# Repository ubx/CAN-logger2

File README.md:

# ESP32 CAN Logger for CANaerospace with WiFi File Browser

This project implements a **dual-mode ESP32 application** for capturing and storing CAN bus data onto an SD card, \
while also providing a temporary WiFi access point with a web-based file browser to retrieve logged data.

---

## Features

### WiFi File Browser
- **WiFi SoftAP Setup** with WPA/WPA2 authentication.
- **Dynamic SSID Generation** based on ESP32 MAC address.
- **Web-based File Browser**:
  - Displays SD card files in a clean HTML table.
  - Supports file size display in human-readable format (KB, MB, GB).
  - Click-to-download functionality with MIME type detection.
- **Automatic Session Timeout**
  - Tracks last HTTP activity.
  - Shuts down after configurable inactivity time.
---

### CAN Logging System
- **CAN Bus Support (TWAI Driver)**
  - Configured for **500 kbit/s**.
  - Accepts all CAN frames.
  - Reliable driver startup with retry on failure.
- **SD Card Logging**
  - Files named sequentially as `CANxxxxx.LOG`.
  - Automatic **old file cleanup** if free space < 2 GB (reclaims up to 4 GB).
  - Efficient batch writes with **32 KB buffering**.
  - Uses `fsync()` to ensure data integrity.
- **Logging Format**
  - Each CAN frame stored as:
    ```
    (timestamp) can <ID>#<DATA>
    ```  
    Example:
    ```
    (1755839938.123456) can 123#11AAFF
    ```
- **Task-based Architecture**
  - `CAN_RX Task`: Receives frames from TWAI driver.
  - `CAN_Proc Task`: Formats messages into log lines.
  - `SD_Writer Task`: Buffers and writes batches to SD card.
- **Runtime Monitoring**
  - Tracks total message count.
  - Periodic logging of statistics to console.

---

## Technical Highlights
- **FreeRTOS Queues** for decoupled CAN reception and SD writing.
- **High-throughput SD logging** using buffered I/O.
- **Failsafe Storage Management** with automatic cleanup.
- **Lightweight Web Server** (ESP-IDF HTTPD) for SD browsing and downloads.
- **No RTC dependency**: Uses a fictional start timestamp to emulate Unix time.
- **Tested on an ESP32-S3 board:** [ESP32-S3 1.64inch AMOLED Touch Display Development Board](https://www.waveshare.com/esp32-s3-touch-amoled-1.64.htm) with a SANDISK Ultra \
  64 GB, microSDXC, U1, UHS-I.
- **Performance Test**: Running `cangen can0 -D i -I i -L 4 -g 0.5` resulted in a transmission rate of \
approximately 1,800 messages per second.
- **Power consumption**: Web server: 473 mW; Logger with display on: 420 mW; Logger with display off: 440 mW.
---

## Typical Use Case
1. **Power up device** → ESP32 starts in **WiFi AP mode** with SD card accessible via browser.
2. **Download / inspect past CAN logs** through the web interface.
3. **After inactivity timeout** → Device switches into **logging mode**, continuously recording
4. CAN traffic onto the SD card.

---

## Pin-to-Pin Wiring Table

| ESP32 Pin | Function       | Connected To                | Notes                        |
|-----------|----------------|-----------------------------|------------------------------|
| GPIO1     | SPI MOSI       | SD Card MOSI                | Data out from ESP32 → SD     |
| GPIO3     | SPI MISO       | SD Card MISO                | Data in from SD → ESP32      |
| GPIO2     | SPI SCLK       | SD Card SCLK                | SPI clock                    |
| GPIO41    | SPI CS         | SD Card CS                  | Chip select                  |
| GPIO9     | CS             | LCD Chip Select             | Active low                   |
| GPIO10    | PCLK           | LCD SPI Clock / Pixel Clock | QSPI clock                   |
| GPIO11    | DATA0          | LCD Data 0 (D0)             | QSPI data line               |
| GPIO12    | DATA1          | LCD Data 1 (D1)             | QSPI data line               |
| GPIO13    | DATA2          | LCD Data 2 (D2)             | QSPI data line               |
| GPIO14    | DATA3          | LCD Data 3 (D3)             | QSPI data line               |
| GPIO21    | RST            | LCD Reset                   | Optional, active low         
| GPIO18    | CAN TX         | CAN Transceiver TXD         | Transmit to CAN bus          |
| GPIO17    | CAN RX         | CAN Transceiver RXD         | Receive from CAN bus         |
| 3V3       | Power          | SD Card VCC, CAN VCC        | Ensure 3.3V compatible       |
| GND       | Ground         | SD Card GND, CAN GND        | Common ground reference      |
| CANH/—    | —              | CAN Bus High Line           | Differential bus line        |
| CANL/—    | —              | CAN Bus Low Line            | Differential bus line        |

## Recommended Parts List

### Core Components
- **ESP32 Development Board**
  - Example: ESP32-DevKitC, ESP32-WROOM, or M5Stack Core (if display/UI desired)
  - Must expose SPI pins and GPIOs used in the project

- **SD Card Module (SPI interface)**
  - Example: MicroSD Card Module (3.3V logic, SPI mode support)
  - Ensure 3.3V compatible (no 5V modules without level shifting)
  - MicroSD card, Class 10, A1 or higher, ≥16 GB recommended

- **CAN Transceiver** (connects ESP32 to CAN bus)
  - Example ICs:
    - SN65HVD230 (3.3V, commonly used with ESP32)
    - MCP2551 (5V, requires level shifting for ESP32)
    - TJA1050 (5V, also requires level shifting)
  - Choose based on bus voltage (3.3V-friendly parts are easier)

### Power & Connectivity
- **Stable 5V Supply** (for ESP32 board)
  - ESP32 boards usually regulate down to 3.3V internally
- **Common Ground Reference** between ESP32, SD card, and CAN transceiver
- **CAN Bus Wiring**
  - Twisted pair cable (for CANH & CANL)
  - 120 Ω termination resistors at both bus ends

### Optional / Helpful
- **MicroSD Card Reader** (for PC, to inspect logs directly if needed)
- **USB-to-CAN Adapter** (for testing/logging against a PC CAN interface)
- **Case/Enclosure** to protect the ESP32 + modules in automotive environment
- **For CANaerospace logs**: use [this program](https://github.com/ubx/canlog-correct-ts/blob/master/correct-ts.py) to adjust timestamps.
- **Format SD card**: use [this tool](https://www.sdcard.org/downloads/sd-memory-card-formatter-for-linux/)

### Bill of materials

| Number | Part                                                          | Qty | Picture                                          | 	Source                                                                                                                                                        |
|--------|---------------------------------------------------------------|-----|--------------------------------------------------|----------------------------------------------------------------------------------------------------------------------------------------------------------------|
| 1      | ESP32-S3 1.64inch AMOLED<br/> Touch Display Development Board | 1   |   | [AMOLED Touch Display<br/>Development Board](https://www.waveshare.com/esp32-s3-touch-amoled-1.64.htm)                                                         |                                                                                
| 2      | SN65HVD230 CAN Board                                          | 1   |         | [SN65HVD230 CAN Board	](https://www.waveshare.com/sn65hvd230-can-board.htm)                                                                                    |                                                                                      |
| 3      | Step Down Converter Modul                                     | 1   |         | [Step Down Converter Modul	](https://de.aliexpress.com/item/1005006461126809.html?spm=a2g0o.order_list.order_list_main.76.1a475c5fBDXy9Z&gatewayAdapt=glo2deu) |
| 4      | M12 5 Pin Cable Connector                                     | 1   |  | [M12 5 Pin Cable Connector](https://de.aliexpress.com/item/1005008983446794.html?spm=a2g0o.order_list.order_list_main.60.1a475c5fBDXy9Z&gatewayAdapt=glo2deu)  |
| 5      | micro sd card                                                 | 1   |                      |
| 6      | M2x5 round screw                                              | 4   |                                                  |                                                                                                                                                                |
| 7      | M2.5x5 countersunk screw                                      | 1   |
| 8      | M2.5x4 insert                                                 | 1   |
| 9      | Optional:<br/>SD-TF-extension-cable                           | 1   |        | [SD-TF-extension-cable	](https://de.aliexpress.com/item/1005005671622003.html?spm=a2g0o.order_list.order_list_main.4.3fb05c5fkolpFm&gatewayAdapt=glo2deu)      |

---

## Troubleshooting: sdQueue full / canQueue full warnings
If you see warnings like:
- W (xxxx) CAN_Proc: sdQueue full, dropped line
- W (xxxx) CAN_RX: canQueue full, dropped

it means the producer tasks (CAN reception/formatting) are temporarily faster than the consumer (SD writer). \
The firmware includes several mitigations:

Additional steps you can take
- Use a fast SD card (A1/A2 or High Endurance) and keep it healthy/formatted (FAT32).
- Reduce other workload while logging (disable unnecessary peripherals, WiFi, or display if not needed).
- If you still experience drops, you can increase queue depths in src/logger/logging.cpp:
  - CAN_QUEUE_LEN: number of CAN frame buffered between driver and formatter.
  - SD_QUEUE_LEN: number of formatted lines buffered before SD writing.
    Be mindful that increasing these consumes internal RAM.
- If your board has PSRAM, keep it enabled. The logger uses a large batch buffer to write in big chunks for higher throughput.
- Ensure stable 3.3 V supply. Brownouts can slow peripherals and the filesystem.

Notes
- Even with a high-rate CAN traffic (e.g., ~1200 msgs/s), a proper SD card and power supply should avoid drops in most cases.
- If absolute losslessness is required, consider reducing CAN bus load, increasing queue sizes, or writing in binary \
to reduce per-message overhead.

## Todo
- Check display z-distance.
- PCB, move modules up 2mm z-distance.
- PCB, bigger holes for CAN connector cables.
- Check usb hole, make it more tolerant.
- Better lid locking.

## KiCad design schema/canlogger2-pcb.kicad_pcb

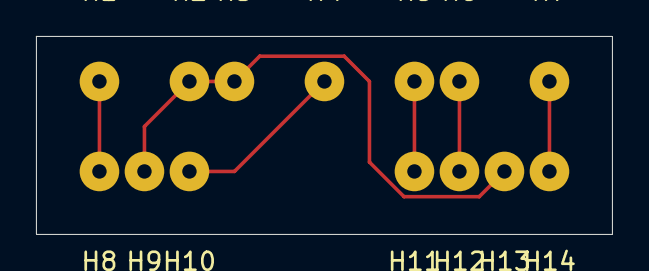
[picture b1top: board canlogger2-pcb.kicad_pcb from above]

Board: 2 copper layers, 32.0 x 11.0 mm, 14 parts (0 on the bottom side), 6 nets.

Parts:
H1: 5V; ConnectingHole_0.8mm_M2_DIN965_Pad
H2, H3, H9, H13: GND; ConnectingHole_0.8mm_M2_DIN965_Pad
H4: 12V; ConnectingHole_0.8mm_M2_DIN965_Pad
H5: Tx; ConnectingHole_0.8mm_M2_DIN965_Pad
H6: Rx; ConnectingHole_0.8mm_M2_DIN965_Pad
H7, H14: 3.3V; ConnectingHole_0.8mm_M2_DIN965_Pad
H8: Vo; ConnectingHole_0.8mm_M2_DIN965_Pad
H10: Vi; ConnectingHole_0.8mm_M2_DIN965_Pad
H11: TX; ConnectingHole_0.8mm_M2_DIN965_Pad
H12: RX; ConnectingHole_0.8mm_M2_DIN965_Pad

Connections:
unnamed: H1.1, H8.1
unnamed: H4.1, H10.1
unnamed: H5.1, H11.1
unnamed: H6.1, H12.1
unnamed: H2.1, H3.1, H9.1, H13.1
unnamed: H7.1, H14.1

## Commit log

2025-08-28 Initial.
2025-08-28 Update tested board link.
2025-08-28 Any line starting with * is ignored silently.
2025-08-28 Avoid previous ID logic goes out of sync. Add messages/sec calculation.
2025-08-28 Allow search gap changes.
2025-08-28 Print Can Id with leading zeros.
2025-08-28 Increase search gap changes.
2025-08-28 Remove unnecessary 5 min delay.
2025-08-28 Misc updates.
2025-08-28 Optimizations.
2025-08-28 Adjust performance test result.
2025-08-29 Revert "Adjust performance test result."
    This reverts commit d90abc59ce624ce9f990937cb5ee36541d906322.
2025-08-29 Create LICENSE
2025-08-29 Add CANaerospace hint.
2025-09-03 Add app info.
2025-09-04 Show PSRAM if present.
2025-09-06 Change spi config.
    New board is https://www.waveshare.com/esp32-s3-touch-amoled-1.64.htm
    Old was https://www.waveshare.com/wiki/ESP32-S3-Touch-AMOLED-1.75
2025-09-07 Move source to src directory.
2025-09-07 Set board flash and psram size.
2025-09-07 Remove unuseds return parameter.
2025-09-08 Allow read flash size.
2025-09-08 Add LVGL stuff, wip.
2025-09-11 Works without display.
2025-09-11 Update espressif32.
2025-09-11 Refactoring.
2025-09-11 Add case.
2025-09-16 Prepare for lvgl.
2025-09-16 Add gui stuff.
2025-09-16 Runs, but nothing is displayed!
2025-09-16 Use MALLOC_CAP_SPIRAM.
2025-09-16 Do not use use_qspi_interface.
2025-09-17 Rework, works, but no info displayed.
2025-09-17 Rework, works and info displayed!
2025-09-17 Add more info displayed!
2025-09-17 Add amoled display pins.
2025-09-17 Set background color, increase buffer size.
2025-09-18 Show app name and version numver. Increase idle time.
2025-09-18 Rework, optimized, cosmetic.
2025-09-18 Back to LV_FONT_MONTSERRAT_26. LV_FONT_MONTSERRAT_28 don't work properly.
2025-09-21 Large batch buffer moved to heap/PSRAM to save internal DRAM for queues. Update readme.
2025-09-21 Update readme with picture.
2025-09-21 Update readme.
2025-09-22 Turn off display after 5 min. logging to avoid burn-in risk. Bump version.
2025-09-22 Tune buffer size. Update readme.
2025-09-22 Tune buffer size. Delete lvgl_task when not used. Update README.
2025-09-26 Use listen-only mode, TWAI_MODE_LISTEN_ONLY.
2025-09-26 Add housing lid with sd card.
2025-09-26 Update power consumption and BOM.
2025-09-26 Bump version.
2025-09-28 Optimize.
2025-09-28 Complete README.md
2025-09-30 Add sd card image.
2025-09-30 Add test program to test if a SD card to meet A1/A2 requirements.
2025-10-03 Update sd card stuff.
2025-10-03 Update performance test result.
2025-10-04 Minor cosmetic changes.
2025-10-05 Fix log line length truncation issue. Bump version.
2025-10-06 Update bom.
2025-10-06 Add new 3d housing files.
2025-10-12 Update housing files.
2025-10-12 Small change of sd card position and size.
2025-10-18 Add pcb and wiring.
2025-10-19 New wiring diagram, add todo.
2025-10-20 Update todo.
